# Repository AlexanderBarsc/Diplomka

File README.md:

# Diplomka
Všechno potřebné pro diplomku
Tady odkaz na samotnou práci: https://www.overleaf.com/5378626868ssqpxgxytjcf

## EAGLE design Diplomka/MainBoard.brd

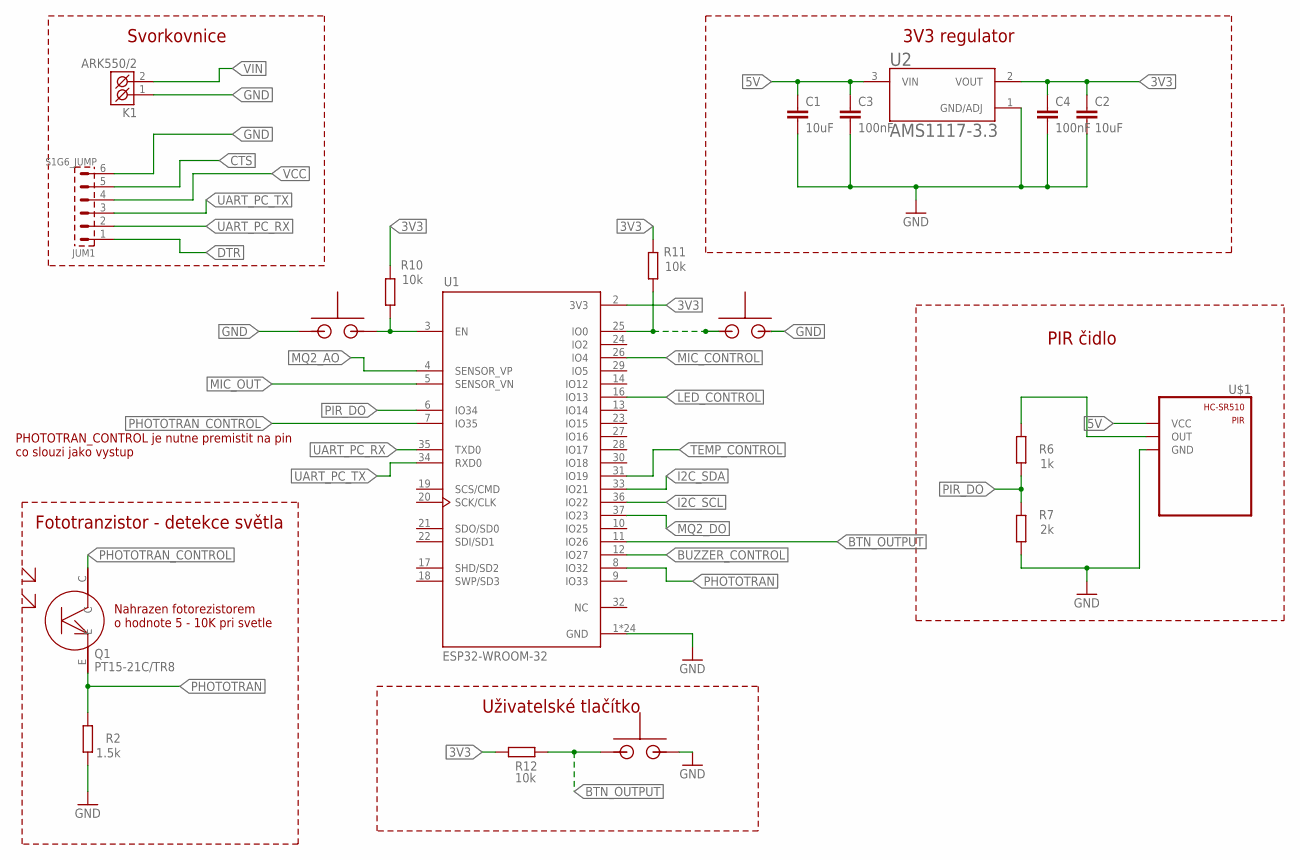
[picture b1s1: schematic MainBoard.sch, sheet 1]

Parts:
C1, C2: 10uF; C0805
C3, C4: 100nF; C0805
JUM1: S1G6_JUMP; S1G6_JUM
K1: ARK550/2
Q1: PT15-21C/TR8
R2: 1.5k; R0805
R6: 1k; R0805
R7: 2k; R0805
R10, R11, R12: 10k; R0805
U1: ESP32-WROOM-32; MODULE_ESP32-WROOM-32
U2: AMS1117-3.3; SOT229P700X180-4N
U$1: HC-SR501
U$6, U$7, U$8: TS6604B

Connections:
3V3: C2.1, C4.1, R10.2, R11.2, R12.2, U1.2 (3V3), U2.2 (VOUT)
5V: C1.1, C3.1, U2.3 (VIN), U$1.VCC; also elsewhere on the board
BTN_OUTPUT: R12.1, U1.11 (IO26), U$8.+
BUZZER_CONTROL: U1.12 (IO27); also elsewhere on the board
CTS: JUM1.5; also elsewhere on the board
DTR: JUM1.1; also elsewhere on the board
EN: R10.1, U1.3 (EN), U$6.+; also elsewhere on the board
GND: C1.2, C2.2, C3.2, C4.2, JUM1.6, K1.1 (K1), R2.1, R7.1, U1.1 (GND), U1.15 (GND), U1.38 (GND), U1.39_1 (GND), U1.39_2 (GND), U1.39_3 (GND), U1.39_4 (GND), U1.39_5 (GND), U1.39_6 (GND), U1.39_7 (GND), U1.39_8 (GND), U1.39_9 (GND), U1.39_10 (GND), U1.39_11 (GND), U1.39_12 (GND), U1.39_13 (GND), U1.39_14 (GND), U1.39_15 (GND), U1.39_16 (GND), U1.39_17 (GND), U1.39_18 (GND), U1.39_19 (GND), U1.39_20 (GND), U1.39_21 (GND), U2.1 (GND/ADJ), U$1.GND, U$6.-, U$7.-, U$8.-; also elsewhere on the board
I2C_SCL: U1.36 (IO22); also elsewhere on the board
I2C_SDA: U1.33 (IO21); also elsewhere on the board
IO0: R11.1, U1.25 (IO0), U$7.+; also elsewhere on the board
LED_CONTROL: U1.16 (IO13); also elsewhere on the board
MIC_CONTROL: U1.26 (IO4); also elsewhere on the board
MIC_OUT: U1.5 (SENSOR_VN); also elsewhere on the board
MQ2_AO: U1.4 (SENSOR_VP); also elsewhere on the board
MQ2_DO: U1.37 (IO23); also elsewhere on the board
unnamed: R6.2, U$1.OUT
PHOTOTRAN: Q1.E, R2.2, U1.8 (IO32)
PHOTOTRAN_CONTROL: Q1.C, U1.7 (IO35)
PIR_DO: R6.1, R7.2, U1.6 (IO34)
TEMP_CONTROL: U1.31 (IO19); also elsewhere on the board
UART_PC_RX: JUM1.2, U1.35 (TXD0)
UART_PC_TX: JUM1.3, U1.34 (RXD0)
VCC: JUM1.4
VIN: K1.2 (K2); also elsewhere on the board

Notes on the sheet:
Svorkovnice
3V3 regulator
PIR čidlo
Fototranzistor - detekce světla
Uživatelské tlačítko
Nahrazen fotorezistorem o hodnote 5 - 10K pri svetle
PHOTOTRAN_CONTROL je nutne premistit na pin co slouzi jako vystup

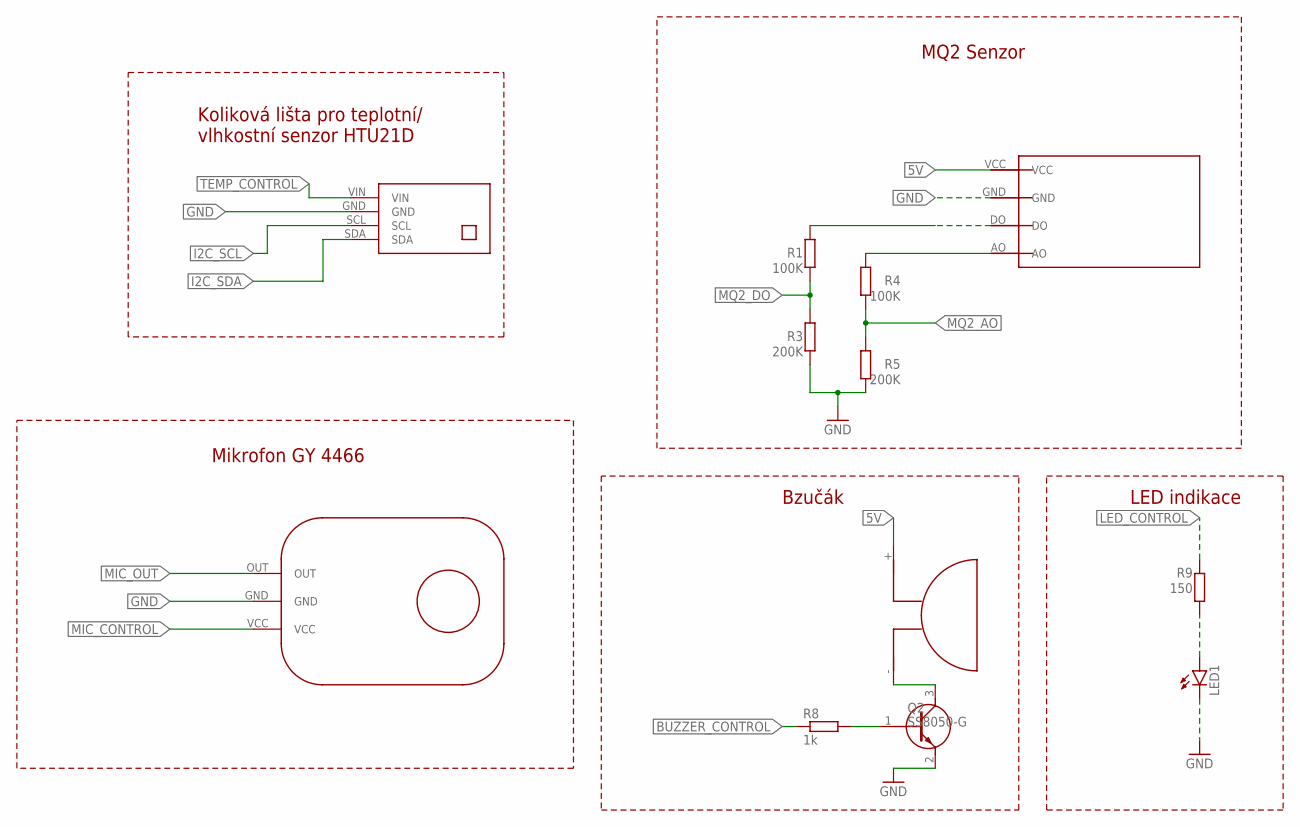
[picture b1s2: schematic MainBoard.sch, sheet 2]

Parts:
LED1: LEDCHIP-LED0805; CHIP-LED0805
Q2: SS8050-G; SOT95P240X115-3N
R1, R4: 100K; R0805
R3, R5: 200K; R0805
R8: 1k; R0805
R9: 150; R0805
U$2: MQ2
U$3: GY4466
U$4: BUZZER
U$5: HTU21D

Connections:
5V: U$2.VCC, U$4.+; also elsewhere on the board
BUZZER_CONTROL: R8.1; also elsewhere on the board
GND: LED1.C, Q2.2 (E), R3.1, R5.1, U$2.GND, U$3.GND, U$5.GND; also elsewhere on the board
I2C_SCL: U$5.SCL; also elsewhere on the board
I2C_SDA: U$5.SDA; also elsewhere on the board
LED_CONTROL: R9.2; also elsewhere on the board
MIC_CONTROL: U$3.VCC; also elsewhere on the board
MIC_OUT: U$3.OUT; also elsewhere on the board
MQ2_AO: R4.1, R5.2; also elsewhere on the board
MQ2_DO: R1.1, R3.2; also elsewhere on the board
unnamed: Q2.3 (C), U$4.-
unnamed: Q2.1 (B), R8.2
unnamed: R1.2, U$2.DO
unnamed: R4.2, U$2.AO
unnamed: LED1.A, R9.1
TEMP_CONTROL: U$5.VIN; also elsewhere on the board

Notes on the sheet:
Koliková lišta pro teplotní/ vlhkostní senzor HTU21D
MQ2 Senzor
Mikrofon GY 4466
Bzučák
LED indikace

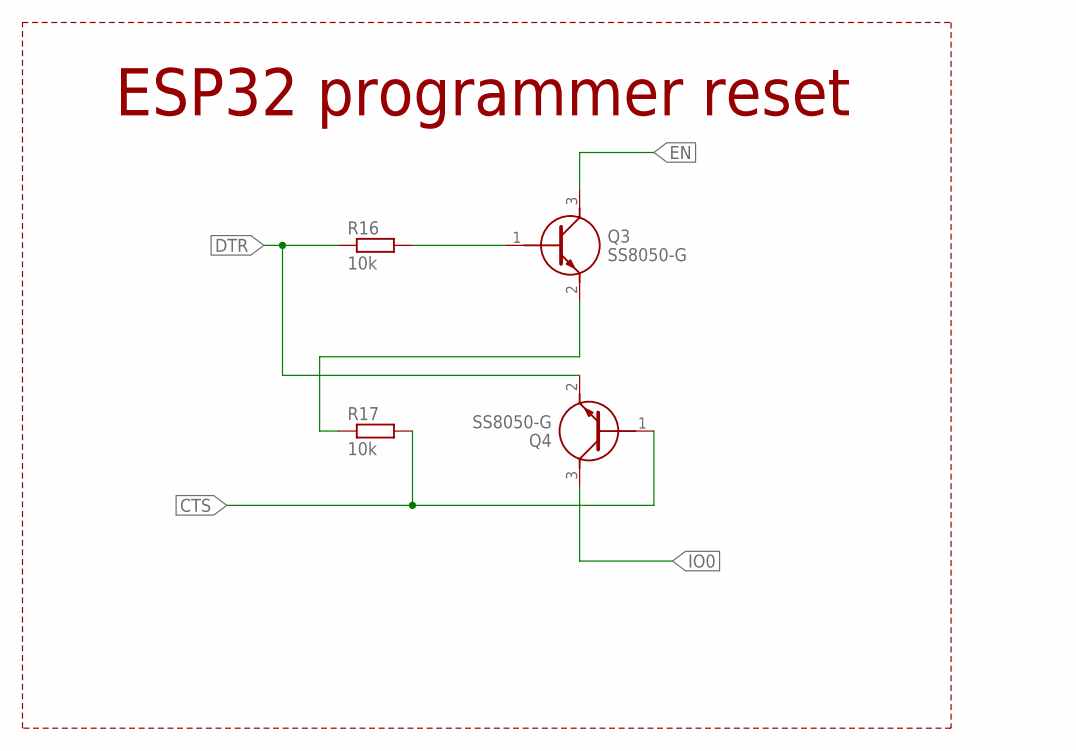
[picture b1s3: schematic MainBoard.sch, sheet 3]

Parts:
Q3, Q4: SS8050-G; SOT95P240X115-3N
R16, R17: 10k; R0805

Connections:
CTS: Q4.1 (B), R17.2; also elsewhere on the board
DTR: Q4.2 (E), R16.1; also elsewhere on the board
EN: Q3.3 (C); also elsewhere on the board
IO0: Q4.3 (C); also elsewhere on the board
unnamed: Q3.1 (B), R16.2
unnamed: Q3.2 (E), R17.1

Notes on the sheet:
ESP32 programmer reset

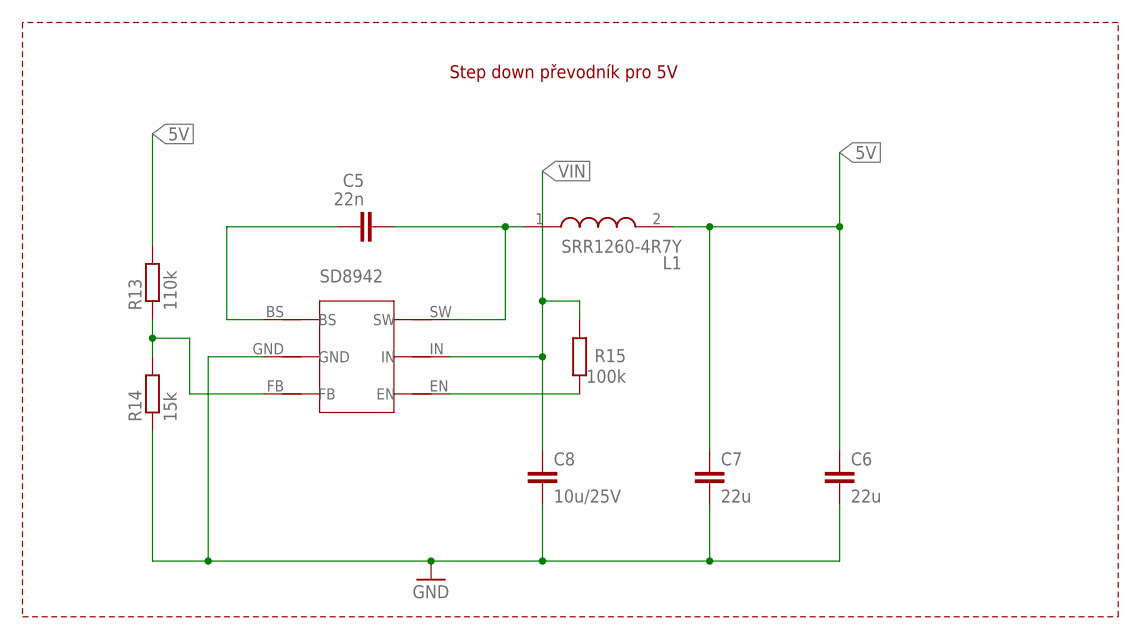
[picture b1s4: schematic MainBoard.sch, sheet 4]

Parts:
C5: 22n; C0805
C6, C7: 22u; C0805
C8: 10u/25V; C0805
L1: SRR1260-4R7Y; SRR12604R7Y
R13: 110k; R0805
R14: 15k; R0805
R15: 100k; R0805
U$9: SD8942

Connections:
5V: C6.1, C7.1, L1.2, R13.2; also elsewhere on the board
GND: C6.2, C7.2, C8.2, R14.1, U$9.GND; also elsewhere on the board
unnamed: C5.1, U$9.BS
unnamed: C5.2, L1.1, U$9.SW
unnamed: R15.1, U$9.EN
unnamed: R13.1, R14.2, U$9.FB
VIN: C8.1, R15.2, U$9.IN; also elsewhere on the board

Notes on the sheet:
Step down převodník pro 5V
SD8942

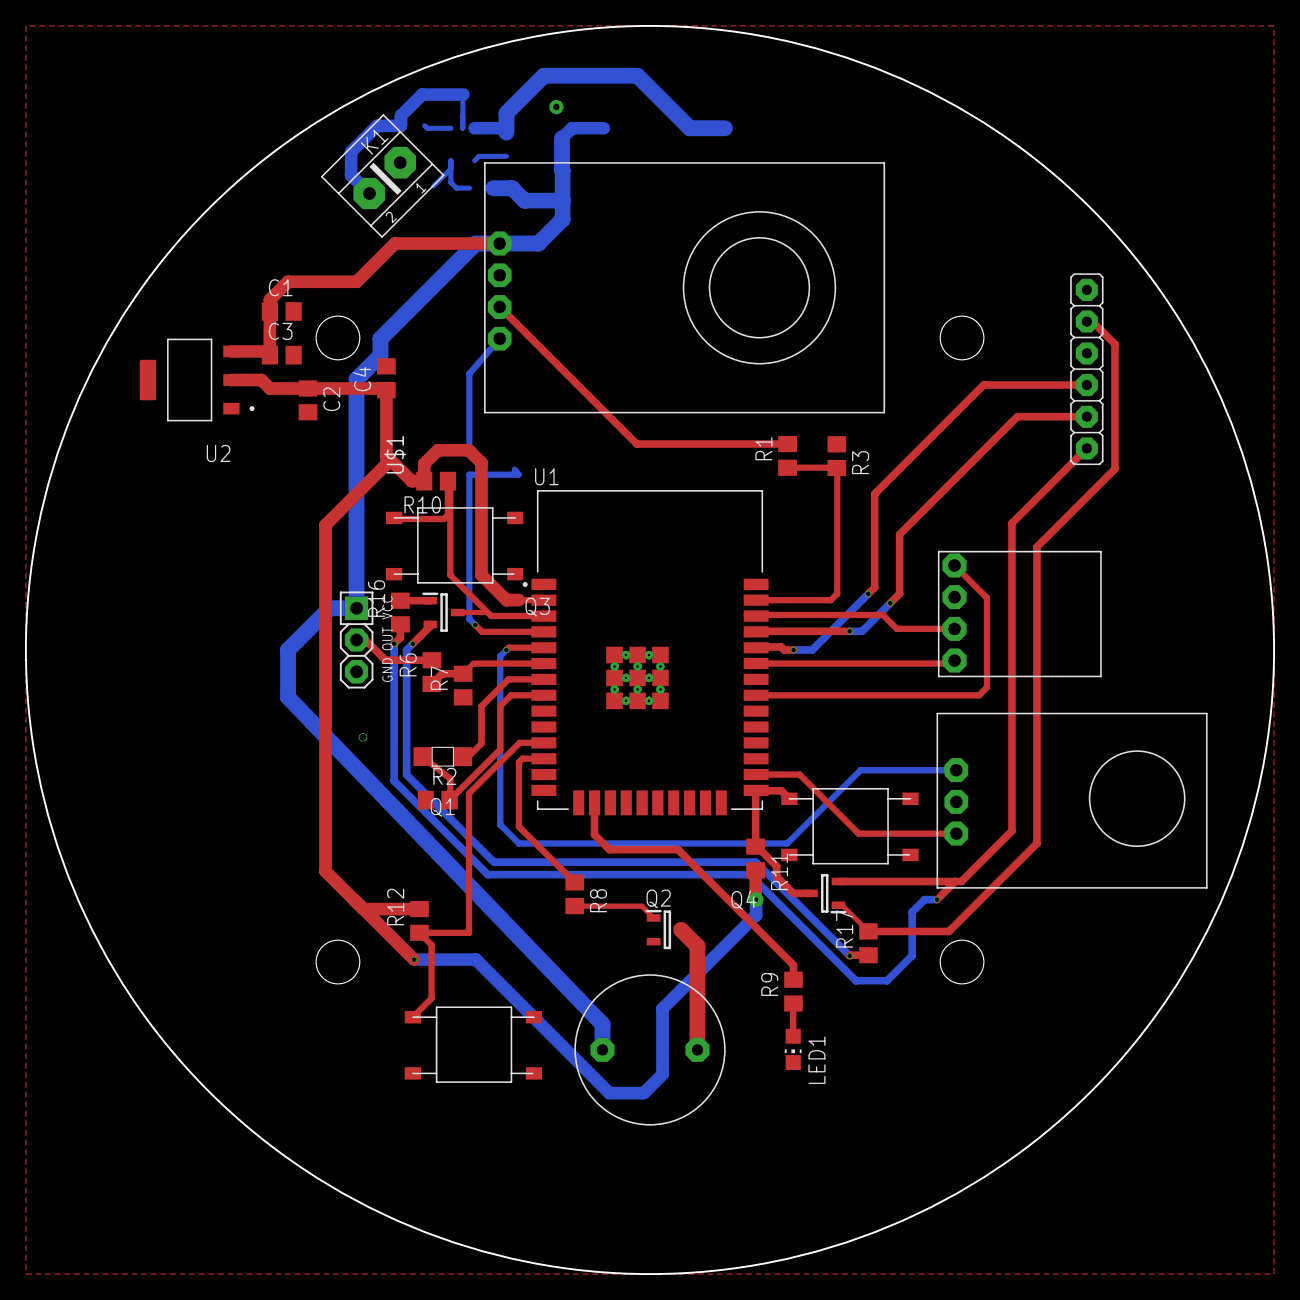
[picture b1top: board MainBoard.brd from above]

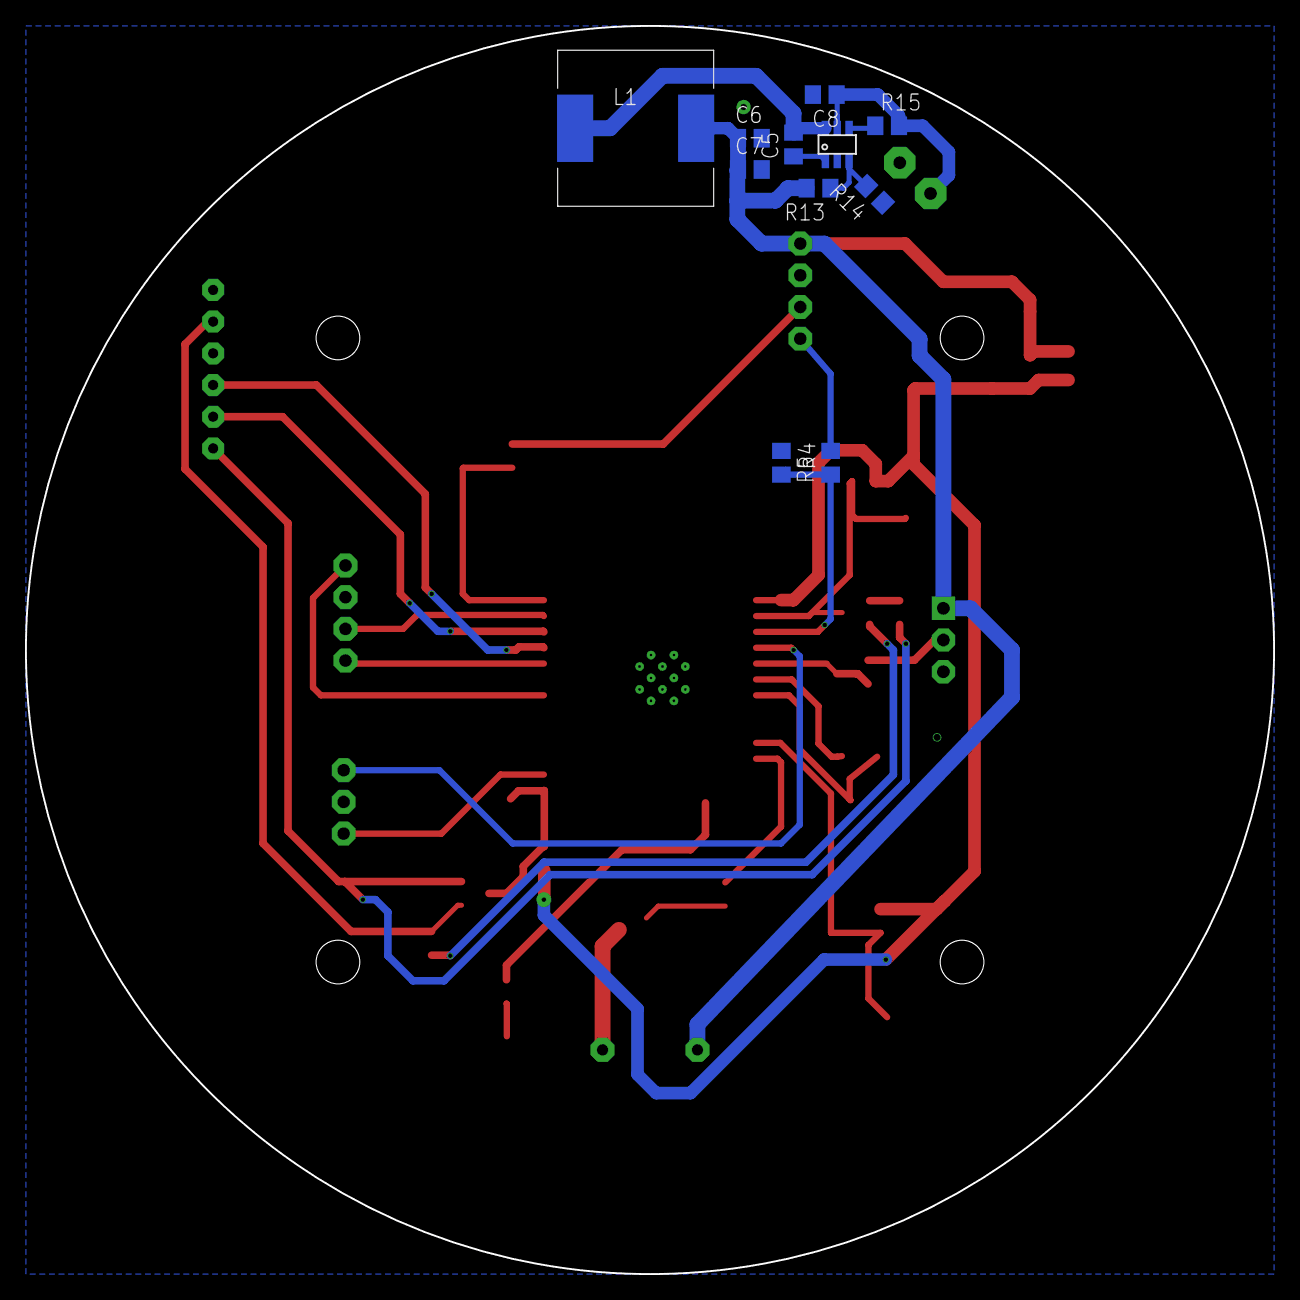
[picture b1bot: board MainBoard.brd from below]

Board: 2 copper layers, 100.0 x 100.0 mm, 45 parts (11 on the bottom side), 35 nets.

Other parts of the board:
U$10: A4L-LOC

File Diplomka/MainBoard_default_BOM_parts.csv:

"Part";"Value";"Device";"Package";"Library";"Description";"AVAILABILITY";"CHECK_PRICES";"DESCRIPTION";"HEIGHT";"MANUFACTURER_NAME";"MANUFACTURER_PART_NUMBER";"MF";"MOUSER_PART_NUMBER";"MOUSER_PRICE-STOCK";"MP";"PACKAGE";"POPULARITY";"PRICE";"SNAPEDA_LINK";"SPICEPREFIX";
"C1";"10uF";"C-EUC0805";"C0805";"rcl";"CAPACITOR, European symbol";"";"";"";"";"";"";"";"";"";"";"";"88";"";"";"C";
"C2";"10uF";"C-EUC0805";"C0805";"rcl";"CAPACITOR, European symbol";"";"";"";"";"";"";"";"";"";"";"";"88";"";"";"C";
"C3";"100nF";"C-EUC0805";"C0805";"rcl";"CAPACITOR, European symbol";"";"";"";"";"";"";"";"";"";"";"";"88";"";"";"C";
"C4";"100nF";"C-EUC0805";"C0805";"rcl";"CAPACITOR, European symbol";"";"";"";"";"";"";"";"";"";"";"";"88";"";"";"C";
"C5";"22n";"C-EUC0805";"C0805";"rcl";"CAPACITOR, European symbol";"";"";"";"";"";"";"";"";"";"";"";"88";"";"";"C";
"C6";"22u";"C-EUC0805";"C0805";"rcl";"CAPACITOR, European symbol";"";"";"";"";"";"";"";"";"";"";"";"88";"";"";"C";
"C7";"22u";"C-EUC0805";"C0805";"rcl";"CAPACITOR, European symbol";"";"";"";"";"";"";"";"";"";"";"";"88";"";"";"C";
"C8";"10u/25V";"C-EUC0805";"C0805";"rcl";"CAPACITOR, European symbol";"";"";"";"";"";"";"";"";"";"";"";"88";"";"";"C";
"JUM1";"S1G6_JUMP";"S1G6_JUMP";"S1G6_JUM";"#PaJa_konektory";"Radove konektory - koliky - 6x";"";"";"";"";"";"";"";"";"";"";"";"";"";"";"";
"K1";"ARK550/2";"ARK550/2";"ARK550/2";"#PaJa_konektory";"Svorkovnice - roztec 3,5mm - dvojita";"";"";"";"";"";"";"";"";"";"";"";"";"";"";"";
"L1";"SRR1260-4R7Y";"SRR1260-4R7Y";"SRR12604R7Y";"SRR1260-4R7Y";"Inductor Power Shielded Wirewound 4.7uH 30% 100KHz 19Q-Factor Ferrite 6.8A 15.5mOhm DCR T/R";"";"";"Inductor Power Shielded Wirewound 4.7uH 30% 100KHz 19Q-Factor Ferrite 6.8A 15.5mOhm DCR T/R";"6.5mm";"Bourns";"SRR1260-4R7Y";"";"652-SRR1260-4R7Y";"https://www.mouser.co.uk/ProductDetail/Bourns/SRR1260-4R7Y?q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";"";"";"";"";"";"";
"LED1";"";"LEDCHIP-LED0805";"CHIP-LED0805";"led";"LED";"";"";"";"";"";"";"";"";"";"";"";"68";"";"";"";
"Q1";"PT15-21C/TR8";"PT15-21C/TR8";"PT15-21C/TR8";"myParts";"";"";"";"";"";"";"";"";"";"";"";"";"";"";"";"";
"Q2";"BC817-40LT1SMD";"BC817-40LT1SMD";"SOT23-BEC";"transistor-npn";"NPN Transistor";"";"";"";"";"";"";"";"";"";"";"";"10";"";"";"";
"Q3";"SS8050-G";"SS8050-G";"SOT95P240X115-3N";"SS8050-G";"Bipolar Transistors - BJT NPN TRANSISTOR 1.5A 40V";"";"";"Bipolar Transistors - BJT NPN TRANSISTOR 1.5A 40V";"1.15mm";"Comchip Technology";"SS8050-G";"";"750-SS8050-G";"https://www.mouser.co.uk/ProductDetail/Comchip-Technology/SS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";"";"";"";"";"";"";
"Q4";"SS8050-G";"SS8050-G";"SOT95P240X115-3N";"SS8050-G";"Bipolar Transistors - BJT NPN TRANSISTOR 1.5A 40V";"";"";"Bipolar Transistors - BJT NPN TRANSISTOR 1.5A 40V";"1.15mm";"Comchip Technology";"SS8050-G";"";"750-SS8050-G";"https://www.mouser.co.uk/ProductDetail/Comchip-Technology/SS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";"";"";"";"";"";"";
"R1";"1K";"R-EU_R0805";"R0805";"rcl";"RESISTOR, European symbol";"";"";"";"";"";"";"";"";"";"";"";"86";"";"";"R";
"R2";"1.5k";"R-EU_R0805";"R0805";"rcl";"RESISTOR, European symbol";"";"";"";"";"";"";"";"";"";"";"";"86";"";"";"R";
"R3";"2K";"R-EU_R0805";"R0805";"rcl";"RESISTOR, European symbol";"";"";"";"";"";"";"";"";"";"";"";"86";"";"";"R";
"R4";"1K";"R-EU_R0805";"R0805";"rcl";"RESISTOR, European symbol";"";"";"";"";"";"";"";"";"";"";"";"86";"";"";"R";
"R5";"2K";"R-EU_R0805";"R0805";"rcl";"RESISTOR, European symbol";"";"";"";"";"";"";"";"";"";"";"";"86";"";"";"R";
"R6";"1k";"R-EU_R0805";"R0805";"rcl";"RESISTOR, European symbol";"";"";"";"";"";"";"";"";"";"";"";"86";"";"";"R";
"R7";"2k";"R-EU_R0805";"R0805";"rcl";"RESISTOR, European symbol";"";"";"";"";"";"";"";"";"";"";"";"86";"";"";"R";
"R8";"1k";"R-EU_R0805";"R0805";"rcl";"RESISTOR, European symbol";"";"";"";"";"";"";"";"";"";"";"";"86";"";"";"R";
"R9";"150";"R-EU_R0805";"R0805";"rcl";"RESISTOR, European symbol";"";"";"";"";"";"";"";"";"";"";"";"86";"";"";"R";
"R10";"10k";"R-EU_R0805";"R0805";"rcl";"RESISTOR, European symbol";"";"";"";"";"";"";"";"";"";"";"";"86";"";"";"R";
"R11";"10k";"R-EU_R0805";"R0805";"rcl";"RESISTOR, European symbol";"";"";"";"";"";"";"";"";"";"";"";"86";"";"";"R";
"R12";"10k";"R-EU_R0805";"R0805";"rcl";"RESISTOR, European symbol";"";"";"";"";"";"";"";"";"";"";"";"86";"";"";"R";
"R13";"110k";"R-EU_R0805";"R0805";"rcl";"RESISTOR, European symbol";"";"";"";"";"";"";"";"";"";"";"";"86";"";"";"R";
"R14";"15k";"R-EU_R0805";"R0805";"rcl";"RESISTOR, European symbol";"";"";"";"";"";"";"";"";"";"";"";"86";"";"";"R";
"R15";"100k";"R-EU_R0805";"R0805";"rcl";"RESISTOR, European symbol";"";"";"";"";"";"";"";"";"";"";"";"86";"";"";"R";
"R16";"10k";"R-EU_R0805";"R0805";"rcl";"RESISTOR, European symbol";"";"";"";"";"";"";"";"";"";"";"";"86";"";"";"R";
"R17";"10k";"R-EU_R0805";"R0805";"rcl";"RESISTOR, European symbol";"";"";"";"";"";"";"";"";"";"";"";"86";"";"";"R";
"U$1";"HC-SR501";"HC-SR501";"HC-SR501";"Sensors_PIR_Lux";"PIR Module HC-SR501";"";"";"";"";"";"";"";"";"";"";"";"";"";"";"";
"U$2";"MQ2";"MQ2";"MQ2";"myParts";"";"";"";"";"";"";"";"";"";"";"";"";"";"";"";"";
"U$3";"GY4466";"GY4466";"GY4466";"myParts";"mikrofon GY466";"";"";"";"";"";"";"";"";"";"";"";"";"";"";"";
"U$4";"BUZZER";"BUZZER";"BUZZER";"myParts";"generický bzučák o průměru 12mm";"";"";"";"";"";"";"";"";"";"";"";"";"";"";"";
"U$5";"HTU21D";"HTU21D";"HTU21D";"myParts";"htu21d";"";"";"";"";"";"";"";"";"";"";"";"";"";"";"";
"U$6";"TS6604B";"TS6604B";"TS6604B";"myParts";"smd tlacitko";"";"";"";"";"";"";"";"";"";"";"";"";"";"";"";
"U$7";"TS6604B";"TS6604B";"TS6604B";"myParts";"smd tlacitko";"";"";"";"";"";"";"";"";"";"";"";"";"";"";"";
"U$8";"TS6604B";"TS6604B";"TS6604B";"myParts";"smd tlacitko";"";"";"";"";"";"";"";"";"";"";"";"";"";"";"";
"U$9";"SD8942";"SD8942";"SD8942";"myParts";"step-down";"";"";"";"";"";"";"";"";"";"";"";"";"";"";"";
"U1";"ESP32-WROOM-32";"ESP32-WROOM-32";"MODULE_ESP32-WROOM-32";"ESP32-WROOM-32";"Check availability";"Not in stock";"https://www.snapeda.com/parts/ESP32-WROOM-32/Espressif+Syste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";" Bluetooth, WiFi 802.11b/g/n, Bluetooth v4.2 +EDR, Class 1, 2 and 3 Transceiver Module 2.4GHz ~ 2.5GHz Antenna Not Included, U.FL Surface Mount ";"";"";"";"Espressif Systems";"";"";"ESP32-WROOM-32";"Non Standard Espressif Systems";"";"None";"https://www.snapeda.com/parts/ESP32-WROOM-32/Espressif+Syste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";"";
"U2";"AMS1117-3.3";"AMS1117-3.3";"SOT229P700X180-4N";"AMS1117-3.3";"Check availability";"Not in stock";"https://www.snapeda.com/parts/AMS1117-3.3/Advanced+Monolithi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";" Sot223/Pkg 1-Amp 3.3-Volt Low Drop Out Voltage Regulatator ";"";"";"";"Advanced Monolithic Systems";"";"";"AMS1117-3.3";"SOT-223 Seeed Technology";"";"None";"https://www.snapeda.com/parts/AMS1117-3.3/Advanced+Monolithi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";"";

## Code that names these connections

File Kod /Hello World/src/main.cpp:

#include <Arduino.h>
#include <Wire.h>
#include "Adafruit_HTU21DF.h"

Adafruit_HTU21DF htu = Adafruit_HTU21DF();

#define PHOTOTRAN_CONTROL 25
#define BUZZER_CONTROL 27
#define LED_CONTROL 13
#define PHOTOTRAN_OUTPUT_AD 32 
#define BUTTON_OUTPUT 26
#define TEMP_CONTROL 19
#define DEFAULT_DELAY 1000
#define MIC_CONTROL 4
#define MIC_OUTPUT 39
#define MQ2_OUTPUT 36
#define PIR_OUTPUT 34

#define I2C_SDA 22
#define I2C_SCL 21

// put function declarations here:
int myFunction(int, int);

void setup() {
  // put your setup code here, to run once:
  Serial.begin(115200);

  pinMode(TEMP_CONTROL, OUTPUT);
  digitalWrite(TEMP_CONTROL, HIGH);

  delay(2000);

  TwoWire I2CBME = TwoWire(0);

  I2CBME.begin(I2C_SDA, I2C_SCL, 400000);

  pinMode(BUTTON_OUTPUT, INPUT);
  

  if (!htu.begin(&I2CBME)) {
    Serial.println("Check circuit. HTU21D not found!");
    while(1)
    {
      
    }
  }

 while(digitalRead(BUTTON_OUTPUT) == true)
  {
    Serial.println("Namerena teplota je: ");
    Serial.println(htu.readTemperature());
    Serial.println("Namerena vlhkost je: ");
    Serial.println(htu.readHumidity());
    delay(DEFAULT_DELAY);
  }

  Serial.println("Testuji zvonek");
  pinMode(BUZZER_CONTROL, OUTPUT);
  digitalWrite(BUZZER_CONTROL, HIGH);
  delay(DEFAULT_DELAY);
  digitalWrite(BUZZER_CONTROL, LOW);
  
  Serial.println("Testuji LED");
  pinMode(LED_CONTROL, OUTPUT);
  digitalWrite(LED_CONTROL, HIGH);

  Serial.println("Nyni testuji tlacitko a fototranzistor");


  pinMode(PHOTOTRAN_CONTROL, OUTPUT);
  digitalWrite(PHOTOTRAN_CONTROL, HIGH);

  int photoValue = 0;
  while(digitalRead(BUTTON_OUTPUT) == true)
  {
    photoValue = analogRead(PHOTOTRAN_OUTPUT_AD);
    Serial.println(photoValue);
    delay(DEFAULT_DELAY);
  }
  Serial.println("Konec testovani");
  delay(DEFAULT_DELAY);
  pinMode(MIC_CONTROL, OUTPUT);
  digitalWrite(MIC_CONTROL, HIGH);

  Serial.println("Nyni testuji mikrofon.");

  while(digitalRead(BUTTON_OUTPUT) == true)
  {
    photoValue = analogRead(MIC_OUTPUT);
    Serial.println(photoValue);
    delay(DEFAULT_DELAY);
  }

  Serial.println("Konec testovani");
  delay(1000);

  Serial.println("Nyni testuji MQ2.");

  while(digitalRead(BUTTON_OUTPUT) == true)
  {
    photoValue = analogRead(MQ2_OUTPUT);
    Serial.println(photoValue);
    delay(DEFAULT_DELAY);
  }

  Serial.println("Nyni testuji PIR");
  delay(1000);
  pinMode(PIR_OUTPUT,INPUT);

  while(digitalRead(BUTTON_OUTPUT) == true)
  {
    Serial.println(digitalRead(PIR_OUTPUT));
    delay(100);
  }


  Serial.println("Vse otestovano, nyni pokracuji v behu programu");



}

void loop() {
  // put your main code here, to run repeatedly:
  Serial.println("Ono to nejak funguje ¯\\_(ツ)_/¯");
  delay(1000);
}

int myFunction(int x, int y) {
  return x + y;
} 

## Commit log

2023-08-20 První práce, importování ESP32 brd knihovny, začátek schématu
2023-08-29 Added battery switch IC to schematic and library. # Please enter the commit message for your changes. Lines starting # with '#' will be ignored, and an empty message aborts the commit. # # On branch 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
2023-08-29 Added libraries for TI parts.
2023-09-04 Test on mac
2023-09-10 Added some useful files.
2023-09-10 Pridan regulator pro 3V3
2023-09-12 Added phototransistor
2023-09-19 Some more WIP.
2023-09-24 Hotová první verze schématu
2023-09-24 Schema v1.0 hotovo
2023-09-24 WIP.
2023-09-24 Přidána aktuální diplomka a schémata plošného spoje ve formátu pdf.
2023-09-29 Nektere soucastky nyni budou napajene z ESP32. Pridan soubor co obsahuje kosik v GME.
2023-10-01 Zmeny v PCB
2023-10-01 Přidány do repozitáře pravidla JLCPCB, nakresleno PCB asi z 70%ˇ.
2023-10-14 Přidán stepdown converted. Třeba dodat vhodnou cívku a dokreslit desku.
2023-10-15 Cca hotový plošňák, třeba udělat nějaké úpravy ale jinak dobré.
2023-10-18 Opravena rozteč.
2023-10-18 Design hotový, čas importovat bitmapu.
2023-10-18 Přidány výrobní data
2023-10-18 Přidán rozumný fototranzistor.
2023-10-21 Přidán aktualizovaný seznam součástek
2023-10-21 Udělána objednávka.
2023-10-27 Přidána faktura
2024-02-25 Added code example.
2024-02-26 Implementace nějakého kódu
2024-02-28 Added REST API exemple
2024-03-02 Implemented endpoints for digitalPins GET and POST
2024-03-03 Přidáno přerušení pro PIR
2024-03-03 Got a running example + some adjustments.
2024-03-06 Fixed I2C
2024-03-09 Cleaned up the code a little bit.
2024-03-09 Úprava kódu aby to víc splňovalo požadavky
2024-03-16 Revert "WIP"
    This reverts commit 92520fda2677ff8fd32398182bd15a351072d8fc.
2024-03-16 Pridany timer pro LEDku
2024-03-21 Přidáno pouzdro
2024-04-01 Working solution for now.
2024-04-04 Přidána prezentace
2024-04-08 Odstraněny přebytečné soubory
2024-04-13 Další práce na diplomce.
2024-04-14 More WIP
2024-04-14 Opraveno přetečení časovače
2024-04-14 Some more adjustments.
2024-04-28 Final code version
2024-06-26 Nakreslený stojan.
2024-07-03 Removed buzzer turning on when smoke is detected.
2024-07-21 Added Watchdog
2024-07-27 Zlepšena čitelnost funkce kde dochází k nastavování mikrokontroleru.
2024-08-18 WIP in progress on FTP server.
2024-12-27 Revert "WIP in progress on FTP server."
    This reverts commit 29653f6703d1177db0453c449ee62864c4096a34.

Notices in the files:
parts and their libraries:
Copyright (C) PaJa 2011-2014
